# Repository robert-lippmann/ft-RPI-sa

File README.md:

# ft-RPI-sa
The ft-RPI-sa controller is a versatile enhancement, developed to control models primarily built with fischertechnik but can be also used with Lego or any other kind of technical toy, limited to 12V supply and I/O voltage.
It consists of the main compute board (aka mainboard), covering all the required logic circuitry, and an additional I/O board with all the inputs and outputs to connect to the model. The I/O board features standard mini-banana-plug connectors with a diameter of 2.5mm. The mainboard can  optionally be used as a Raspberry Pi HAT and is supplied by either a battery set or an external 9V power supply.

# Mainboard V2.1 Top View

# Mainboard V2.1 Bottom View

# I/O Board Top View

# Features
 - Using NXP Microcontroller S32K142 or S32K144(W) or S32K146 w/o hardware modification
 - 8 independent 9V inputs (supporting analog & digital input capability with individual
   programable pull configuration)
 - 8 outputs which can be used independently or in combination for brushed or stepper Microcontroller
 - 4 independent 9V counter inputs which can use DMA for counting
 - Using a separate board for I/O connectors
 - Can be used as Raspberry Pi HAT with integrated power supply for the Raspberry Pi
 - Interfaces like UART (TTL), I2C (5V and 3V3), CAN-PHY, SPI (also useable with Raspberry Pi SPI1)
   to be used with additional peripherals
 - RTC incl. 512 Bytes RAM, w/ battery backup, useable for optional timed wakeup/activities
 - Full featured MMBasic interpreter including an editor running on S32K14x using UART
 - MMBasic interpreter enhanced with commands and functions to support on-board peripherals
 - Using a simple terminal program, running either on Raspberry Pi or on a PC/MAC, for SW development
 - Program transfer done via XMODEM up-/download to/from host computer
 - MMBasic program stored in D-Flash memory (64k) of MCU
 - Optional auto start of MMBasic application once powering up
 
# YouTube video
&nbsp;&nbsp;&nbsp;&nbsp;
 - [Video of 2 fischertechnik models controlled by the ft-RPI-sa](https://www.youtube.com/watch?v=sPbV3bQHXdk)

# Copyright and Acknowledgements

MMBasic interpreter:

Thanks to Geoff for granting me the permission to adapt his beautiful MMBasic interpreter to this hardware project and go public with it.
 - https://geoffg.net/micromite.html
 - Copyright 2011-2024 Geoff Graham
 - Copyright 2016-2024 Peter Mather

MMBasic enhancements and modifications related to ft-RPI-sa hardware:
- Copyright 2022-2025 Robert Lippmann
  
ft-RPI-sa Hardware:

- Copyright 2022-2025 Robert Lippmann

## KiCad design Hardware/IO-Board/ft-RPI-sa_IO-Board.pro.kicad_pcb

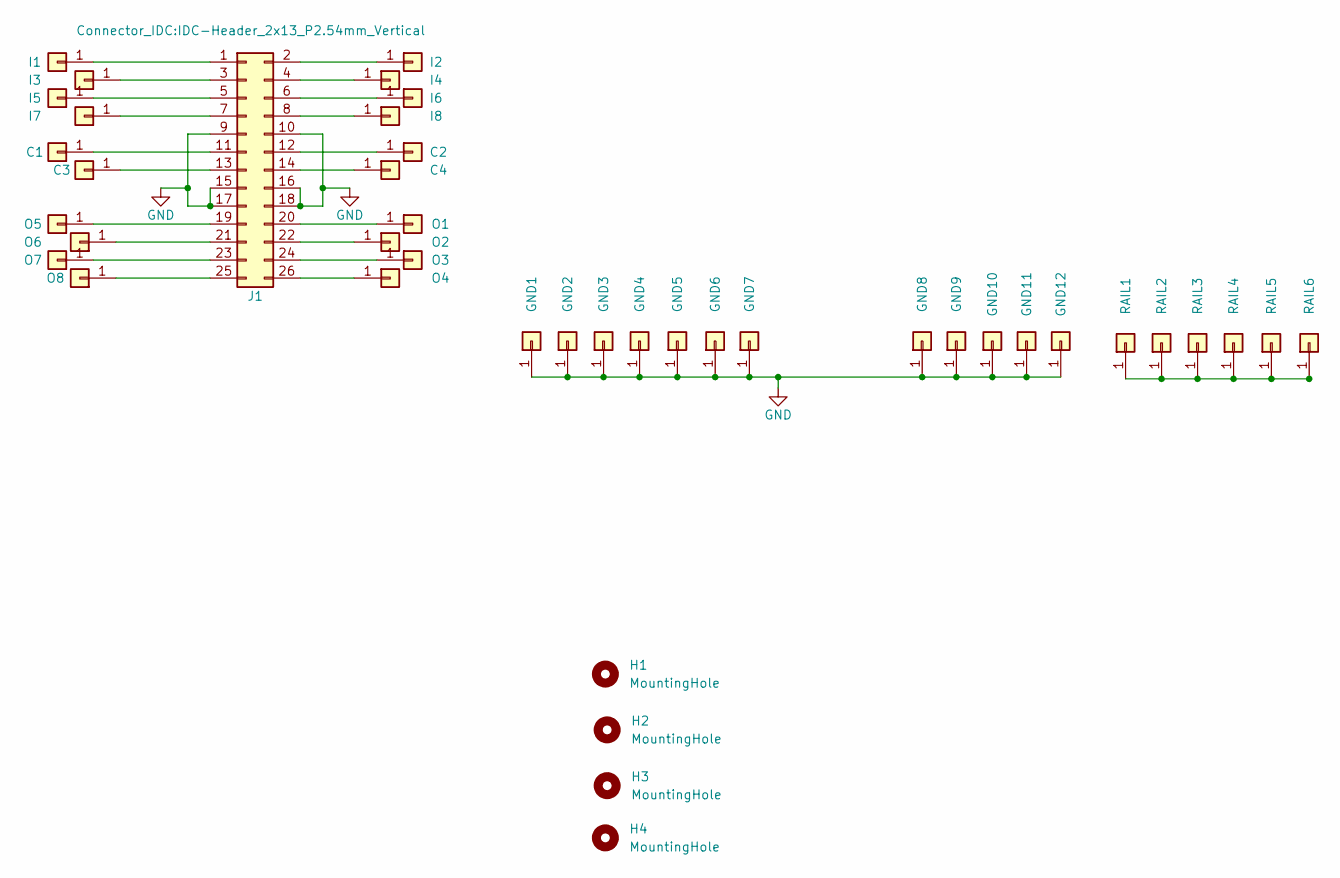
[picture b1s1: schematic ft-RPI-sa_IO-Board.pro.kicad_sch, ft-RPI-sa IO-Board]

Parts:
C1, C2, C3, C4: Conn_01x01; Bundhuelse_3mm
GND1, GND2, GND3, GND4, GND5, GND6, GND7, GND8, GND9, GND10, GND11, GND12: Conn_01x01; Bundhuelse_3mm
H1, H2, H3, H4: MountingHole; MountingHole_3.2mm_M3_DIN965
I1, I2, I3, I4, I5, I6, I7, I8: Conn_01x01; Bundhuelse_3mm
J1: Conn_02x13_Odd_Even; IDC-Header_2x13_P2.54mm_Vertical
O1, O2, O3, O4, O5, O6, O7, O8: Conn_01x01; Bundhuelse_3mm
RAIL1, RAIL2, RAIL3, RAIL4, RAIL5, RAIL6: Conn_01x01; Bundhuelse_3mm

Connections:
GND: GND1.1, GND2.1, GND3.1, GND4.1, GND5.1, GND6.1, GND7.1, GND8.1, GND9.1, GND10.1, GND11.1, GND12.1, J1.9, J1.10, J1.15, J1.16, J1.17, J1.18
unnamed: C1.1, J1.11
unnamed: C2.1, J1.12
unnamed: C3.1, J1.13
unnamed: C4.1, J1.14
unnamed: I1.1, J1.1
unnamed: I2.1, J1.2
unnamed: I3.1, J1.3
unnamed: I4.1, J1.4
unnamed: I5.1, J1.5
unnamed: I6.1, J1.6
unnamed: I7.1, J1.7
unnamed: I8.1, J1.8
unnamed: J1.19, O5.1
unnamed: J1.20, O1.1
unnamed: J1.21, O6.1
unnamed: J1.22, O2.1
unnamed: J1.23, O7.1
unnamed: J1.24, O3.1
unnamed: J1.25, O8.1
unnamed: J1.26, O4.1
unnamed: RAIL1.1, RAIL2.1, RAIL3.1, RAIL4.1, RAIL5.1, RAIL6.1

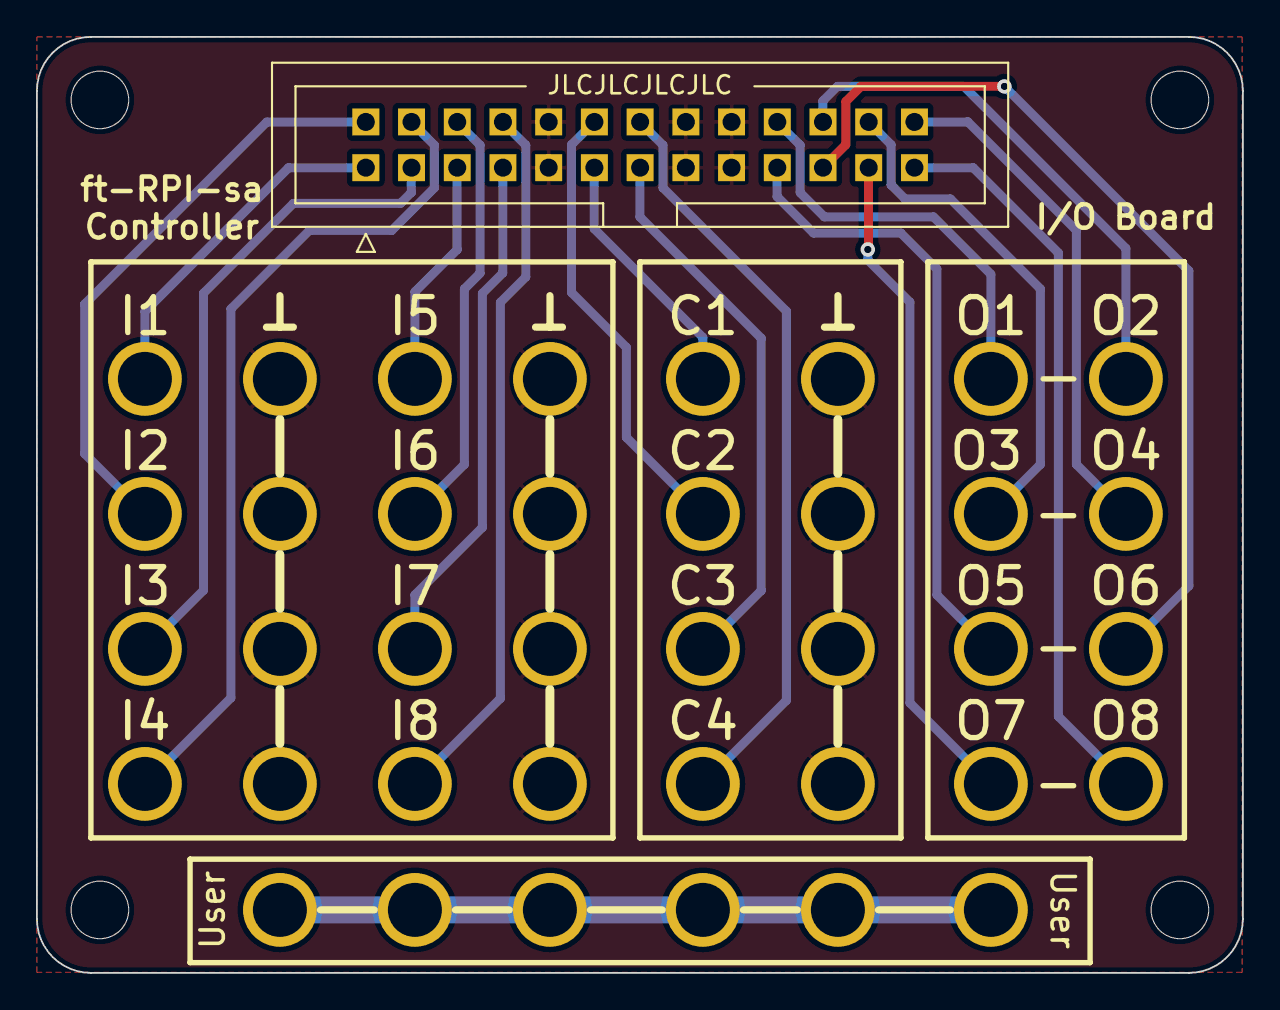
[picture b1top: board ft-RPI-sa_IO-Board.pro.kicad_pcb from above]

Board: 2 copper layers, 67.0 x 52.0 mm, 43 parts (0 on the bottom side), 22 nets.

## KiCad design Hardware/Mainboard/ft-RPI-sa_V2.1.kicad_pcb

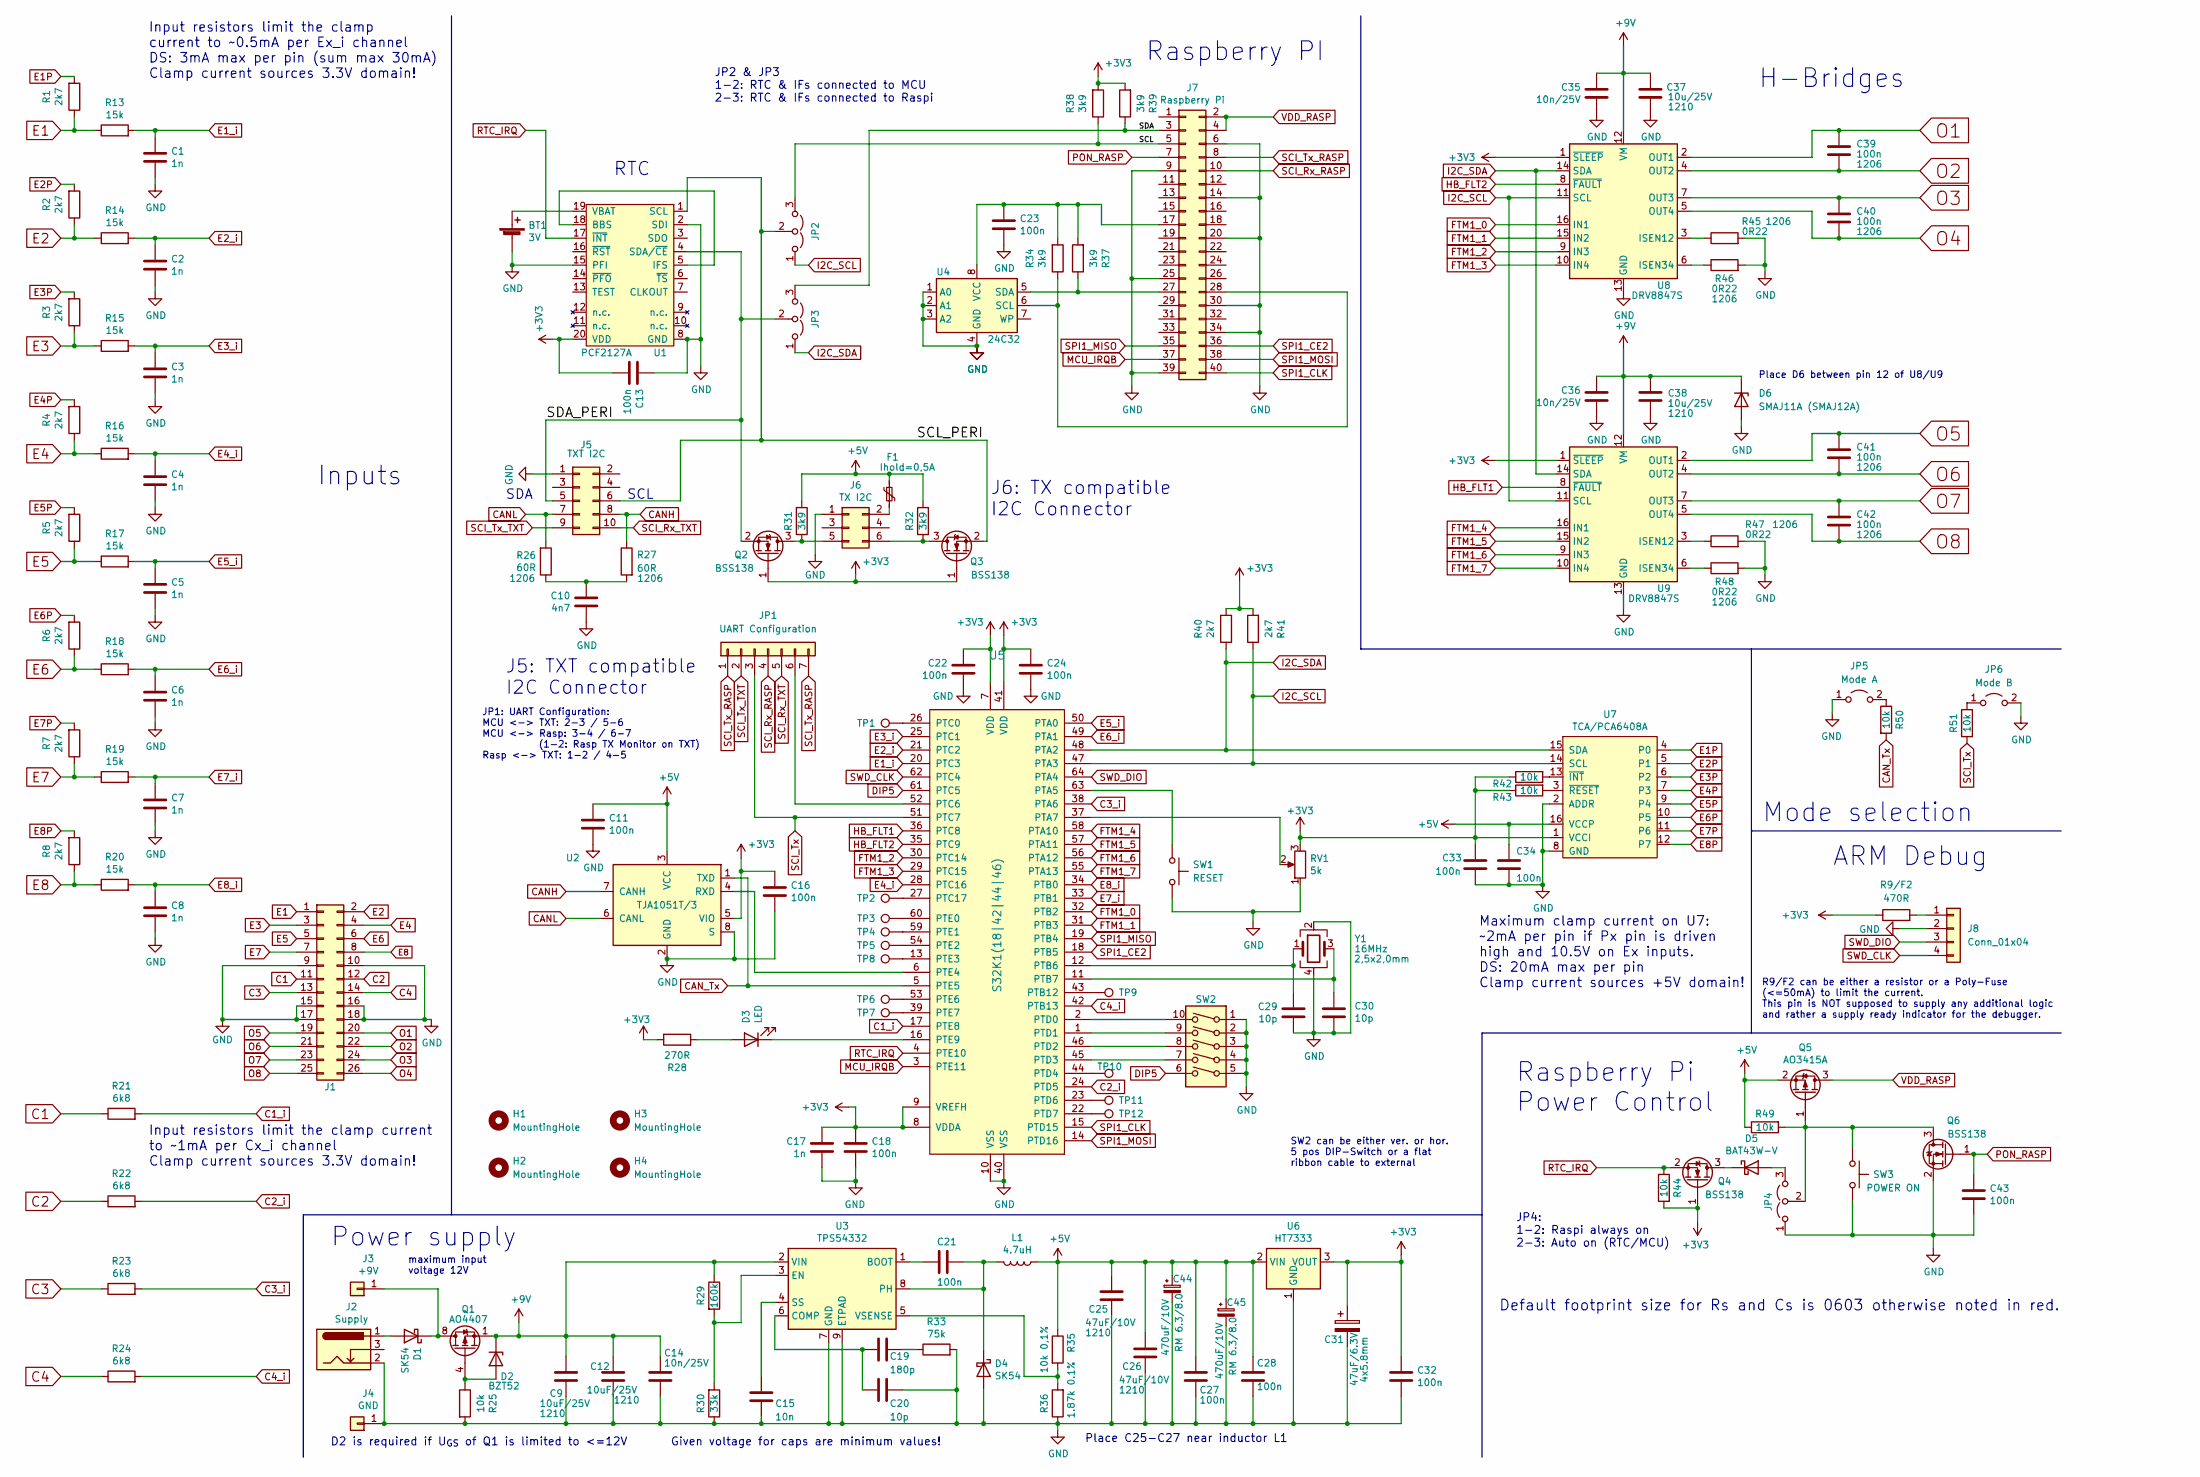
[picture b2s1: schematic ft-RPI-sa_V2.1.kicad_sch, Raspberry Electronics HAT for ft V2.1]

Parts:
BT1: 3V; BatteryHolder_Keystone_1058_1x2032
C1, C2, C3, C4, C5, C6, C7, C8, C17: 1n; C_0603_1608Metric_Pad1.08x0.95mm_HandSolder
C9, C12: 10uF/25V; C_1210_3225Metric_Pad1.33x2.70mm_HandSolder
C10: 4n7; C_0603_1608Metric_Pad1.08x0.95mm_HandSolder
C11, C13, C16, C18, C22, C23, C24, C27, C28, C32, C33, C34, C43: 100n; C_0603_1608Metric_Pad1.08x0.95mm_HandSolder
C14, C35, C36: 10n/25V; C_0603_1608Metric_Pad1.08x0.95mm_HandSolder
C15: 10n; C_0603_1608Metric_Pad1.08x0.95mm_HandSolder
C19: 180p; C_0603_1608Metric_Pad1.08x0.95mm_HandSolder
C20, C29, C30: 10p; C_0603_1608Metric_Pad1.08x0.95mm_HandSolder
C21: 100n; C_0603_1608Metric
C25, C26: 47uF/10V; C_1210_3225Metric_Pad1.33x2.70mm_HandSolder
C31: 47uF/6.3V; C_Elec_4x5.8
C37, C38: 10u/25V; C_1210_3225Metric_Pad1.33x2.70mm_HandSolder
C39, C40, C41, C42: 100n; C_1206_3216Metric_Pad1.33x1.80mm_HandSolder
C44, C45: 470uF/10V; CP_Elec_8x10
D1, D4: SK54; D_SMB
D2: BZT52; D_SOD-323
D3: LED; LED_D3.0mm
D5: BAT43W-V; D_SOD-123
D6: SMAJ11A (SMAJ12A); D_SMA
F1: Ihold=0,5A; R_1206_3216Metric_Pad1.30x1.75mm_HandSolder
H1: MountingHole; MountingHole_2.7mm_M2.5_ISO7380
H2, H3, H4: MountingHole; MountingHole_2.7mm_M2.5_DIN965
J1: Conn_02x13_Odd_Even; IDC-Header_2x13_P2.54mm_Horizontal
J2: Supply; BarrelJack_Horizontal
J3: +9V; 2.6mm Buchse
J4: GND; 2.6mm Buchse
J5: TXT I2C; IDC-Header_2x05_P2.54mm_Horizontal
J6: TX I2C; IDC-Header_2x03_P2.54mm_Horizontal
J7: Raspberry Pi; PinSocket_2x20_P2.54mm_Vertical
J8: Conn_01x04; PinHeader_1x04_P2.54mm_Vertical
JP1: UART Configuration; PinHeader_1x07_P2.00mm_Horizontal
JP2: I2C_SCL; PinHeader_1x03_P2.00mm_Horizontal
JP3: I2C_SDA; PinHeader_1x03_P2.00mm_Horizontal
JP4: RTC SDA; PinHeader_1x03_P2.00mm_Horizontal
JP5: Mode A; PinHeader_1x02_P2.00mm_Horizontal
JP6: Mode B; PinHeader_1x02_P2.00mm_Horizontal
L1: 4.7uH; Fastron_L-242418FPS
Q1: AO4407; SOIC-8_3.9x4.9mm_P1.27mm
Q2, Q3, Q4, Q6: BSS138; SOT-23
Q5: AO3415A; SOT-23
R1, R2, R3, R4, R5, R6, R7, R8, R40, R41: 2k7; R_0603_1608Metric_Pad0.98x0.95mm_HandSolder
R9/F2: 470R; R_0603_1608Metric_Pad0.98x0.95mm_HandSolder
R13, R14, R15, R16, R17, R18, R19, R20: 15k; R_0603_1608Metric_Pad0.98x0.95mm_HandSolder
R21, R22, R23, R24: 6k8; R_0603_1608Metric_Pad0.98x0.95mm_HandSolder
R25, R42, R43, R44, R49, R50, R51: 10k; R_0603_1608Metric_Pad0.98x0.95mm_HandSolder
R26, R27: 60R; R_1206_3216Metric_Pad1.30x1.75mm_HandSolder
R28: 270R; R_0603_1608Metric_Pad0.98x0.95mm_HandSolder
R29: 160k; R_0603_1608Metric_Pad0.98x0.95mm_HandSolder
R30: 33k; R_0603_1608Metric_Pad0.98x0.95mm_HandSolder
R31, R32, R34, R37, R38, R39: 3k9; R_0603_1608Metric_Pad0.98x0.95mm_HandSolder
R33: 75k; R_0603_1608Metric_Pad0.98x0.95mm_HandSolder
R35: 10k 0,1%; R_0603_1608Metric_Pad0.98x0.95mm_HandSolder
R36: 1.87k 0.1%; R_0603_1608Metric_Pad0.98x0.95mm_HandSolder
R45, R46, R47, R48: 0R22; R_1206_3216Metric_Pad1.30x1.75mm_HandSolder
RV1: 5k; Potentiometer_Piher_PT-10-H01_Horizontal
SW1: RESET; SW_Push_1P1T_NO_CK_KMR2
SW2: SW_DIP_x05; DIP-10_W7.62mm_LongPads_LPV
SW3: POWER ON; SW_Tactile_SPST_Angled_PTS645Vx83-2LFS
TP1, TP2, TP3, TP4, TP5, TP6, TP7, TP8, TP9, TP10, TP11, TP12: TestPoint; TestPoint_Pad_D0.8mm_open
U1: PCF2127A; SO-20_12.8x7.5mm_P1.27mm
U2: TJA1051T/3; SOIC-8_3.9x4.9mm_P1.27mm
U3: TPS54332; TI_SO-PowerPAD-8_ThermalVias
U4: 24C32; SOIC-8_3.9x4.9mm_P1.27mm
U5: S32K1(18|42|44|46); LQFP-64_10x10mm_P0.5mm
U6: HT7333; SOT-89-3
U7: TCA/PCA6408A; TSSOP-16_4.4x5mm_P0.65mm
U8, U9: DRV8847S; TSSOP-16_4.4x5mm_P0.65mm
Y1: 16MHz; Crystal_SMD_EuroQuartz_X22-4Pin_2.5x2.0mm

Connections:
+3V3: C13.1, C16.2, C17.2, C18.2, C22.2, C24.1, C31.1, C32.1, C33.1, Q2.1 (G), Q3.1 (G), Q4.1 (G), R9/F2.1, R28.1, R38.2, R39.2, R40.2, R41.2, R42.1, R43.1, R44.2, RV1.3, U1.20 (VDD), U2.5 (VIO), U5.7 (VDD), U5.8 (VDDA), U5.9 (VREFH), U5.41 (VDD), U6.3 (VOUT), U7.1 (VCCI), U8.1 (~SLEEP), U9.1 (~SLEEP)
+5V: C11.2, C25.1, C26.1, C27.1, C28.1, C34.1, C44.1, C45.1, F1.1, L1.1, Q5.2 (S), R31.2, R32.2, R35.1, R49.1, U2.3 (VCC), U6.2 (VIN), U7.16 (VCCP)
+9V: C9.1, C12.1, C14.1, C35.2, C36.2, C37.1, C38.1, D2.1 (K), D6.1 (K), Q1.1 (S), Q1.2 (S), Q1.3 (S), R29.1, U3.2 (VIN), U8.12 (VM), U9.12 (VM)
/SCL: J7.5, JP2.3 (B), R38.1
/SCL_PERI: J5.6, JP2.2 (C), Q3.2 (S), U1.1 (SCL)
/SDA: J7.3, JP3.3 (B), R39.1
/SDA_PERI: J5.5, JP3.2 (C), Q2.2 (S), U1.4 (SDA/~CE)
C1: J1.11, R21.1
C1_i: R21.2, U5.17 (PTE8)
C2: J1.12, R22.1
C2_i: R22.2, U5.24 (PTD5)
C3: J1.13, R23.1
C3_i: R23.2, U5.38 (PTA6)
C4: J1.14, R24.1
C4_i: R24.2, U5.42 (PTB13)
CANH: J5.8, R27.1, U2.7 (CANH)
CANL: J5.7, R26.2, U2.6 (CANL)
CAN_Tx: R50.2, U2.1 (TXD), U5.5 (PTE5)
DIP5: SW2.6, U5.61 (PTC5)
E1: J1.1, R1.1, R13.1
E1P: R1.2, U7.4 (P0)
E1_i: C1.1, R13.2, U5.20 (PTC3)
E2: J1.2, R2.1, R14.1
E2P: R2.2, U7.5 (P1)
E2_i: C2.1, R14.2, U5.21 (PTC2)
E3: J1.3, R3.1, R15.1
E3P: R3.2, U7.6 (P2)
E3_i: C3.1, R15.2, U5.25 (PTC1)
E4: J1.4, R4.1, R16.1
E4P: R4.2, U7.7 (P3)
E4_i: C4.1, R16.2, U5.28 (PTC16)
E5: J1.5, R5.1, R17.1
E5P: R5.2, U7.9 (P4)
E5_i: C5.1, R17.2, U5.50 (PTA0)
E6: J1.6, R6.1, R18.1
E6P: R6.2, U7.10 (P5)
E6_i: C6.1, R18.2, U5.49 (PTA1)
E7: J1.7, R7.1, R19.1
E7P: R7.2, U7.11 (P6)
E7_i: C7.1, R19.2, U5.33 (PTB1)
E8: J1.8, R8.1, R20.1
E8P: R8.2, U7.12 (P7)
E8_i: C8.1, R20.2, U5.34 (PTB0)
FTM1_0: U5.32 (PTB2), U8.16 (IN1)
FTM1_1: U5.31 (PTB3), U8.15 (IN2)
FTM1_2: U5.30 (PTC14), U8.9 (IN3)
FTM1_3: U5.29 (PTC15), U8.10 (IN4)
FTM1_4: U5.58 (PTA10), U9.16 (IN1)
FTM1_5: U5.57 (PTA11), U9.15 (IN2)
FTM1_6: U5.56 (PTA12), U9.9 (IN3)
FTM1_7: U5.55 (PTA13), U9.10 (IN4)
GND: BT1.2 (-), C1.2, C2.2, C3.2, C4.2, C5.2, C6.2, C7.2, C8.2, C9.2, C10.1, C11.1, C12.2, C13.2, C14.2, C15.2, C16.1, C17.1, C18.1, C20.1, C22.1, C23.1, C24.2, C25.2, C26.2, C27.2, C28.2, C29.1, C30.1, C31.2, C32.2, C33.2, C34.2, C35.1, C36.1, C37.2, C38.2, C43.2, C44.2, C45.2, D4.2 (A), D6.2 (A), J1.9, J1.10, J1.15, J1.16, J1.17, J1.18, J2.2, J4.1, J5.1, J6.1, J7.6, J7.9, J7.14, J7.20, J7.25, J7.30, J7.34, J7.39, J8.2, JP4.1 (A), JP5.1 (A), JP6.2 (B), Q6.2 (S), R25.2, R30.1, R33.2, R36.1, R45.2, R46.2, R47.2, R48.2, RV1.1, SW1.2, SW2.1, SW2.2, SW2.3, SW2.4, SW2.5, SW3.2, U1.2 (SDI), U1.8 (GND), U1.15 (PFI), U2.2 (GND), U2.8 (S), U3.7 (GND), U3.9 (ETPAD), U4.1 (A0), U4.2 (A1), U4.3 (A2), U4.4 (GND), U5.10 (VSS), U5.40 (VSS), U6.1 (GND), U7.2 (ADDR), U7.8 (GND), U8.13 (GND), U9.13 (GND), Y1.2, Y1.4
HB_FLT1: U5.36 (PTC8), U9.8 (~FAULT)
HB_FLT2: U5.35 (PTC9), U8.8 (~FAULT)
I2C_SCL: JP2.1 (A), R41.1, U5.47 (PTA3), U7.14 (SCL), U8.11 (SCL), U9.11 (SCL)
I2C_SDA: JP3.1 (A), R40.1, U5.48 (PTA2), U7.15 (SDA), U8.14 (SDA), U9.14 (SDA)
MCU_IRQB: J7.37, U5.3 (PTE11)
unnamed: BT1.1 (+), U1.19 (VBAT)
unnamed: C10.2, R26.1, R27.2
unnamed: C19.1, R33.1
unnamed: D1.2 (A), J2.1
unnamed: D1.1 (K), J3.1, Q1.5 (D), Q1.6 (D), Q1.7 (D), Q1.8 (D)
unnamed: D2.2 (A), Q1.4 (G), R25.1
unnamed: D3.2 (A), R28.2
unnamed: D3.1 (K), U5.16 (PTE9)
unnamed: C21.1, D4.1 (K), L1.2, U3.8 (PH)
unnamed: D5.2 (A), JP4.3 (B)
unnamed: D5.1 (K), Q4.3 (D)
unnamed: F1.2, J6.2
unnamed: J6.5, Q2.3 (D), R31.1
unnamed: J6.6, Q3.3 (D), R32.1
unnamed: C23.2, J7.17, R34.2, R37.2, U4.8 (VCC)
unnamed: J7.27, R37.1, U4.5 (SDA)
unnamed: J7.28, R34.1, U4.6 (SCL)
unnamed: J8.1, R9/F2.2
unnamed: JP1.6, U5.52 (PTC6)
unnamed: JP4.2 (C), Q5.1 (G), Q6.3 (D), R49.2, SW3.1
unnamed: JP5.2 (B), R50.1
unnamed: JP6.1 (A), R51.1
unnamed: U1.5 (IFS), U1.18 (BBS)
unnamed: U2.4 (RXD), U5.6 (PTE4)
unnamed: C21.2, U3.1 (BOOT)
unnamed: C19.2, C20.2, U3.6 (COMP)
unnamed: R29.2, R30.2, U3.3 (EN)
unnamed: C15.1, U3.4 (SS)
unnamed: R35.2, R36.2, U3.5 (VSENSE)
unnamed: SW1.1, U5.63 (PTA5)
unnamed: RV1.2, U5.37 (PTA7)
unnamed: C29.2, U5.12 (PTB6), Y1.1
unnamed: C30.2, U5.11 (PTB7), Y1.3
unnamed: TP9.1, U5.43 (PTB12)
unnamed: TP1.1, U5.26 (PTC0)
unnamed: TP2.1, U5.27 (PTC17)
unnamed: SW2.10, U5.2 (PTD0)
unnamed: SW2.9, U5.1 (PTD1)
unnamed: SW2.8, U5.46 (PTD2)
unnamed: SW2.7, U5.45 (PTD3)
unnamed: TP10.1, U5.44 (PTD4)
unnamed: TP11.1, U5.23 (PTD6)
unnamed: TP12.1, U5.22 (PTD7)
unnamed: TP3.1, U5.60 (PTE0)
unnamed: TP4.1, U5.59 (PTE1)
unnamed: TP5.1, U5.54 (PTE2)
unnamed: TP8.1, U5.13 (PTE3)
unnamed: TP6.1, U5.53 (PTE6)
unnamed: TP7.1, U5.39 (PTE7)
unnamed: R42.2, U7.13 (~INT)
unnamed: R43.2, U7.3 (~RESET)
unnamed: R45.1, U8.3 (ISEN12)
unnamed: R46.1, U8.6 (ISEN34)
unnamed: R47.1, U9.3 (ISEN12)
unnamed: R48.1, U9.6 (ISEN34)
O1: C39.1, J1.20, U8.2 (OUT1)
O2: C39.2, J1.22, U8.4 (OUT2)
O3: C40.1, J1.24, U8.7 (OUT3)
O4: C40.2, J1.26, U8.5 (OUT4)
O5: C41.1, J1.19, U9.2 (OUT1)
O6: C41.2, J1.21, U9.4 (OUT2)
O7: C42.1, J1.23, U9.7 (OUT3)
O8: C42.2, J1.25, U9.5 (OUT4)
PON_RASP: C43.1, J7.7, Q6.1 (G)
RTC_IRQ: Q4.2 (S), R44.1, U1.17 (~INT), U5.4 (PTE10)
SCI_Rx_RASP: J7.10, JP1.4
SCI_Rx_TXT: J5.10, JP1.5
SCI_Tx: JP1.3, R51.2, U5.51 (PTC7)
SCI_Tx_RASP: J7.8, JP1.1, JP1.7
SCI_Tx_TXT: J5.9, JP1.2
SPI1_CE2: J7.36, U5.18 (PTB5)
SPI1_CLK: J7.40, U5.15 (PTD15)
SPI1_MISO: J7.35, U5.19 (PTB4)
SPI1_MOSI: J7.38, U5.14 (PTD16)
SWD_CLK: J8.4, U5.62 (PTC4)
SWD_DIO: J8.3, U5.64 (PTA4)
VDD_RASP: J7.2, J7.4, Q5.3 (D)

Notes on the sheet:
Place C25-C27 near inductor L1
Raspberry PI
Default footprint size for Rs and Cs is 0603 otherwise noted in red.
J6: TX compatible I2C Connector
D2 is required if U_{GS} of Q1 is limited to <=12V
Mode selection
Input resistors limit the clamp current to ~0.5mA per Ex_i channel DS: 3mA max per pin (sum max 30mA) Clamp current sources 3.3V domain!
SCL
Maximum clamp current on U7: ~2mA per pin if Px pin is driven high and 10.5V on Ex inputs. DS: 20mA max per pin Clamp current sources +5V domain!
H-Bridges
Inputs
Power supply
JP2 & JP3 1-2: RTC & IFs connected to MCU 2-3: RTC & IFs connected to Raspi
maximum input voltage 12V
SDA
Raspberry Pi Power Control
SW2 can be either ver. or hor. 5 pos DIP-Switch or a flat ribbon cable to external
J5: TXT compatible I2C Connector
ARM Debug
R9/F2 can be either a resistor or a Poly-Fuse (<=50mA) to limit the current. This pin is NOT supposed to supply any additional logic and rather a supply ready indicator for the debugger.
Place D6 between pin 12 of U8/U9
JP4: 1-2: Raspi always on 2-3: Auto on (RTC/MCU)
JP1: UART Configuration: MCU <-> TXT: 2-3 / 5-6 MCU <-> Rasp: 3-4 / 6-7 (1-2: Rasp TX Monitor on TXT) Rasp <-> TXT: 1-2 / 4-5
Given voltage for caps are minimum values!
Input resistors limit the clamp current to ~1mA per Cx_i channel Clamp current sources 3.3V domain!
RTC

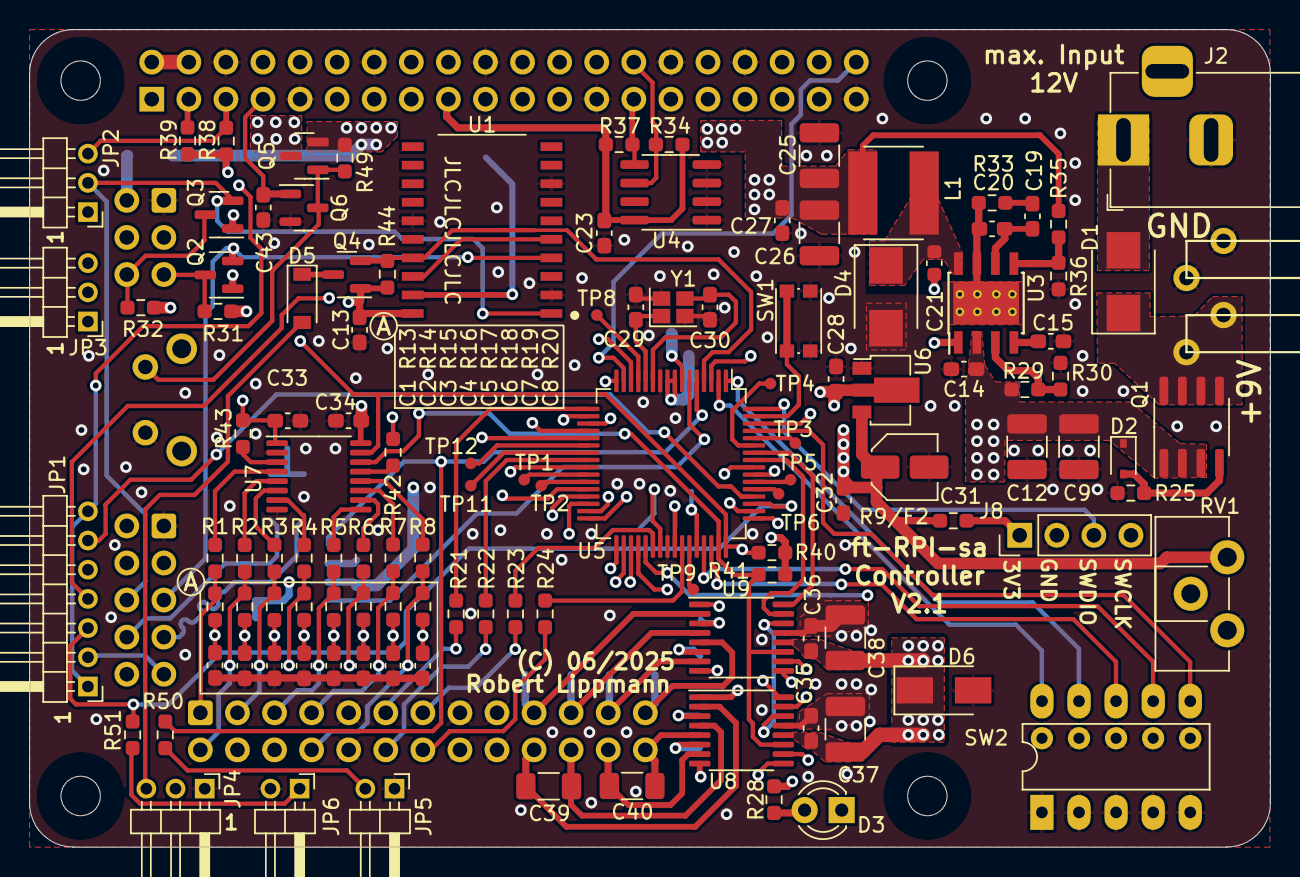
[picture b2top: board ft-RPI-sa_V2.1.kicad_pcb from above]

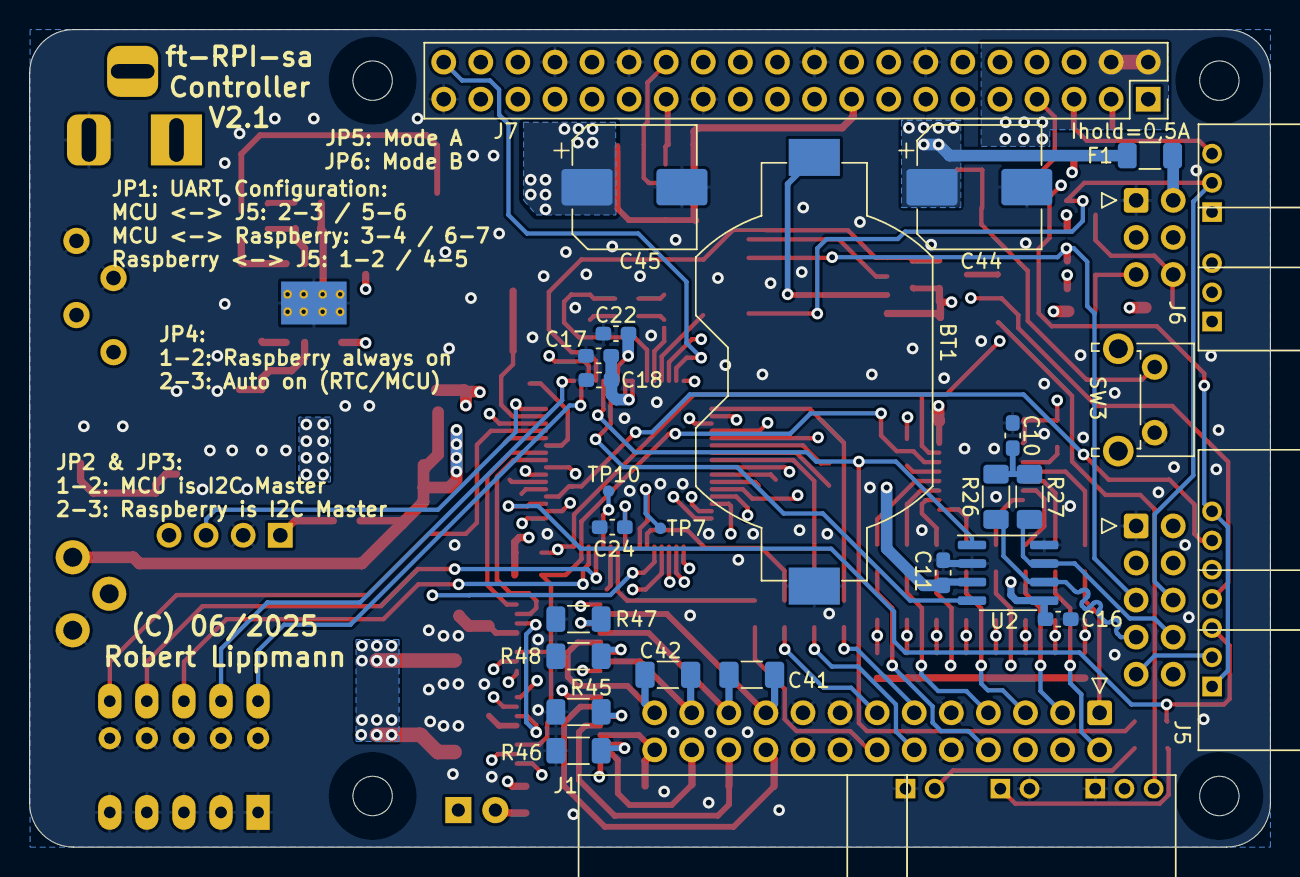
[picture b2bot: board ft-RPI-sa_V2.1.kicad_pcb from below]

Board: 4 copper layers, 85.0 x 56.0 mm, 152 parts (27 on the bottom side), 134 nets.

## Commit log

2025-06-24 Added initial file set

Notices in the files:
Hardware/IO-Board/ft-RPI-sa_IO-Board.pro.kicad_pcb:
(C) 2022 Lippmann Elektronik
